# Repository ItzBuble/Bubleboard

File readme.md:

# Bubleboard

A custom full-size (104-key) mechanical keyboard with a hand-designed PCB, a rotary encoder, an e-ink display and [ZMK](https://zmk.dev) firmware. It was built as my graduation project (maturitní práce) at SPŠ a OA Uherský Brod, field Mechanik elektrotechnik, 2026.

## Features

- 104 keys in a 21 × 6 diode matrix (N-key rollover, no ghosting)
- Seeed XIAO BLE nRF52840 microcontroller soldered directly on the PCB
- Wired USB and Bluetooth Low Energy, with a LiPo battery connected through a JST connector
- Two MCP23017 I/O expanders (I²C) to drive the matrix
- Bourns PEC11L rotary encoder (15 mm) used as a media knob
- nice!view e-ink display (SPI) showing the keyboard status
- Hot-swappable Kailh Choc V1 sockets
- Custom 2-layer PCB designed in KiCad
- 3D-printed case and keycaps
- No backlight, to keep power consumption low

## Hardware

| Part | Component |
| --- | --- |
| Microcontroller | Seeed XIAO BLE nRF52840 |
| I/O expanders | 2× MCP23017 (SSOP), I²C with 10 kΩ pull-ups |
| Switch sockets | 104× Kailh Choc V1 hot-swap |
| Matrix diodes | 105× 1N4148W |
| Rotary encoder | Bourns PEC11L, push button wired into the matrix (Column 16 / Row 0) |
| Display | nice!view, connected over SPI |
| Decoupling | 2× 100 nF and 1× 10 µF |

The PCB was made by JLCPCB and assembled by hand. The schematic and PCB use the [marbastlib](https://github.com/ebastler/marbastlib) library, and the key positions come from a [Keyboard Layout Editor](http://www.keyboard-layout-editor.com) file imported into KiCad.

## Firmware

The firmware is built on ZMK (Zephyr). The matrix is defined in the keyboard's devicetree: columns 0–15 and 16–20 are spread over the two MCP23017 expanders, rows 0–5 are on the second expander, and all pins use `GPIO_ACTIVE_LOW` with pull-ups.

Encoder functions:

- Rotate right: volume up
- Rotate left: volume down
- Press: play / pause

### Building

Firmware is built with GitHub Actions using the standard ZMK user-config workflow. Push a commit (or run the workflow manually from the **Actions** tab) and download the firmware from the build artifacts.

The build uses:

- Board: `seeeduino_xiao_ble`
- Shield: `buble_board` plus `nice_view_adapter` and `nice_view`

The ZMK build needs `config/`, `boards/` and `zephyr/module.yml` to stay in the repository root.

## Case and keycaps

The case was modelled in Autodesk Fusion and 3D printed. It is printed in two halves that are glued together in the middle, with alignment holes and pegs. The PCB is mounted on six screw posts, and a separate display holder (adapted from a freely available model) slides into V-shaped tabs in the top right corner. The keycaps are also 3D printed, adapted from existing models.

## Measurements

Power consumption while connected to a PC (no backlight, no heavy load):

| Meter | V | A | W |
| --- | --- | --- | --- |
| Custom USB meter | 5.092 | 0.005 | 0.027 |
| Commercial USB meter | 5.1080 | 0.0050 | 0.0252 |

Input latency, measured with a 240 fps phone camera (1 frame ≈ 4.167 ms):

| Keyboard | Frames | Latency |
| --- | --- | --- |
| SteelSeries Apex Pro (magnetic) | 8 | 33.3 ms |
| Bubleboard | 11 | 45.8 ms |
| Razer Ornata Chroma (membrane) | 17 | 70.8 ms |
| School membrane keyboard | 19 | 79.2 ms |

## Author

Martin Janíček. Střední průmyslová škola a obchodní akademie Uherský Brod, 2026.

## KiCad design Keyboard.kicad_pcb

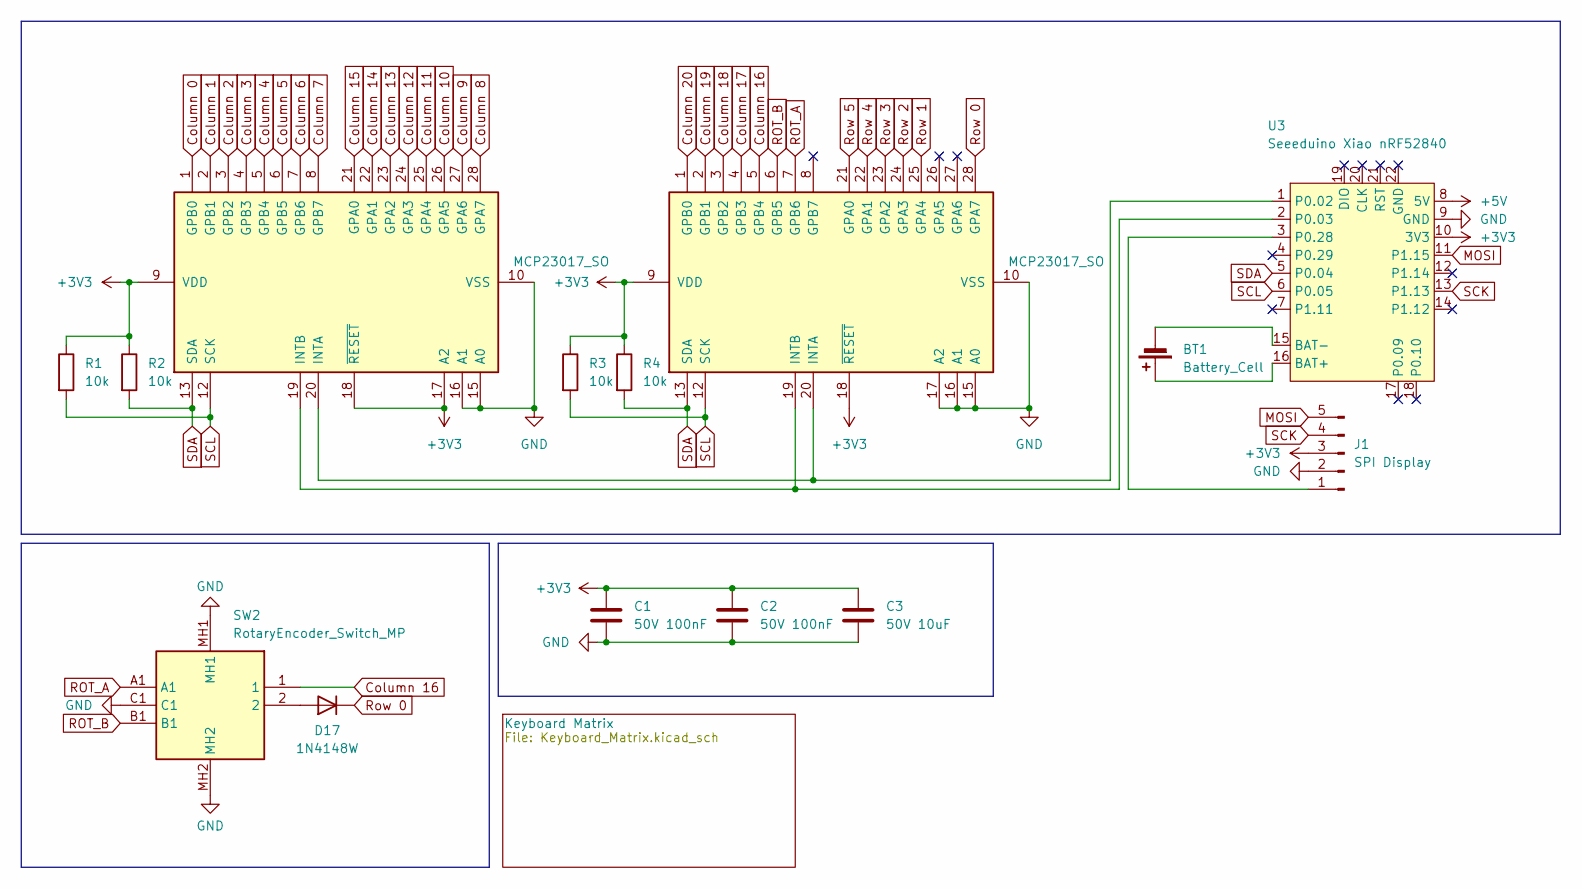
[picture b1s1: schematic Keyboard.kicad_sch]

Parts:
BT1: Battery_Cell
C1, C2: 50V 100nF; C_1206_3216Metric_Pad1.33x1.80mm_HandSolder
C3: 50V 10uF; C_1206_3216Metric_Pad1.33x1.80mm_HandSolder
D17: 1N4148W; D_SOD-123
J1: SPI Display
R1, R2, R3, R4: 10k; R_1206_3216Metric_Pad1.30x1.75mm_HandSolder
SW2: RotaryEncoder_Switch_MP; PEC11L4115FS0020; Mouser Part Number 652-PEC11L4115FS0020
U1, U2: MCP23017_SO; SOIC-28W_7.5x17.9mm_P1.27mm
U3: Seeeduino Xiao nRF52840; Xiao_nRF52840_ACH

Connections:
+3V3: C1.1, C2.1, C3.1, J1.3, R1.1, R2.1, R3.1, R4.1, U1.9 (VDD), U1.17 (A2), U1.18 (~RESET), U2.9 (VDD), U2.18 (~RESET), U3.10 (3V3)
+5V: U3.8 (5V)
Column 0: U1.1 (GPB0); also elsewhere on the board
Column 1: U1.2 (GPB1); also elsewhere on the board
Column 2: U1.3 (GPB2); also elsewhere on the board
Column 3: U1.4 (GPB3); also elsewhere on the board
Column 4: U1.5 (GPB4); also elsewhere on the board
Column 5: U1.6 (GPB5); also elsewhere on the board
Column 6: U1.7 (GPB6); also elsewhere on the board
Column 7: U1.8 (GPB7); also elsewhere on the board
Column 8: U1.28 (GPA7); also elsewhere on the board
Column 9: U1.27 (GPA6); also elsewhere on the board
Column 10: U1.26 (GPA5); also elsewhere on the board
Column 11: U1.25 (GPA4); also elsewhere on the board
Column 12: U1.24 (GPA3); also elsewhere on the board
Column 13: U1.23 (GPA2); also elsewhere on the board
Column 14: U1.22 (GPA1); also elsewhere on the board
Column 15: U1.21 (GPA0); also elsewhere on the board
Column 16: SW2.1, U2.5 (GPB4); also elsewhere on the board
Column 17: U2.4 (GPB3); also elsewhere on the board
Column 18: U2.3 (GPB2); also elsewhere on the board
Column 19: U2.2 (GPB1); also elsewhere on the board
Column 20: U2.1 (GPB0); also elsewhere on the board
GND: C1.2, C2.2, C3.2, J1.2, SW2.C1, SW2.MH1, SW2.MH2, U1.10 (VSS), U1.15 (A0), U1.16 (A1), U2.10 (VSS), U2.15 (A0), U2.16 (A1), U2.17 (A2), U3.9 (GND)
MOSI: J1.5, U3.11 (P1.15)
unnamed: D17.2 (A), SW2.2
unnamed: J1.1, U3.3 (P0.28)
unnamed: BT1.1 (+), U3.16 (BAT+)
unnamed: BT1.2 (-), U3.15 (BAT-)
ROT_A: SW2.A1, U2.7 (GPB6), U3.4 (P0.29)
ROT_B: SW2.B1, U2.6 (GPB5), U3.7 (P1.11)
Row 0: D17.1 (K), U2.28 (GPA7); also elsewhere on the board
Row 1: U2.25 (GPA4); also elsewhere on the board
Row 2: U2.24 (GPA3); also elsewhere on the board
Row 3: U2.23 (GPA2); also elsewhere on the board
Row 4: U2.22 (GPA1); also elsewhere on the board
Row 5: U2.21 (GPA0); also elsewhere on the board
SCK: J1.4, U3.13 (P1.13)
SCL: R1.2, R3.2, U1.12 (SCK), U2.12 (SCK), U3.6 (P0.05)
SDA: R2.2, R4.2, U1.13 (SDA), U2.13 (SDA), U3.5 (P0.04)

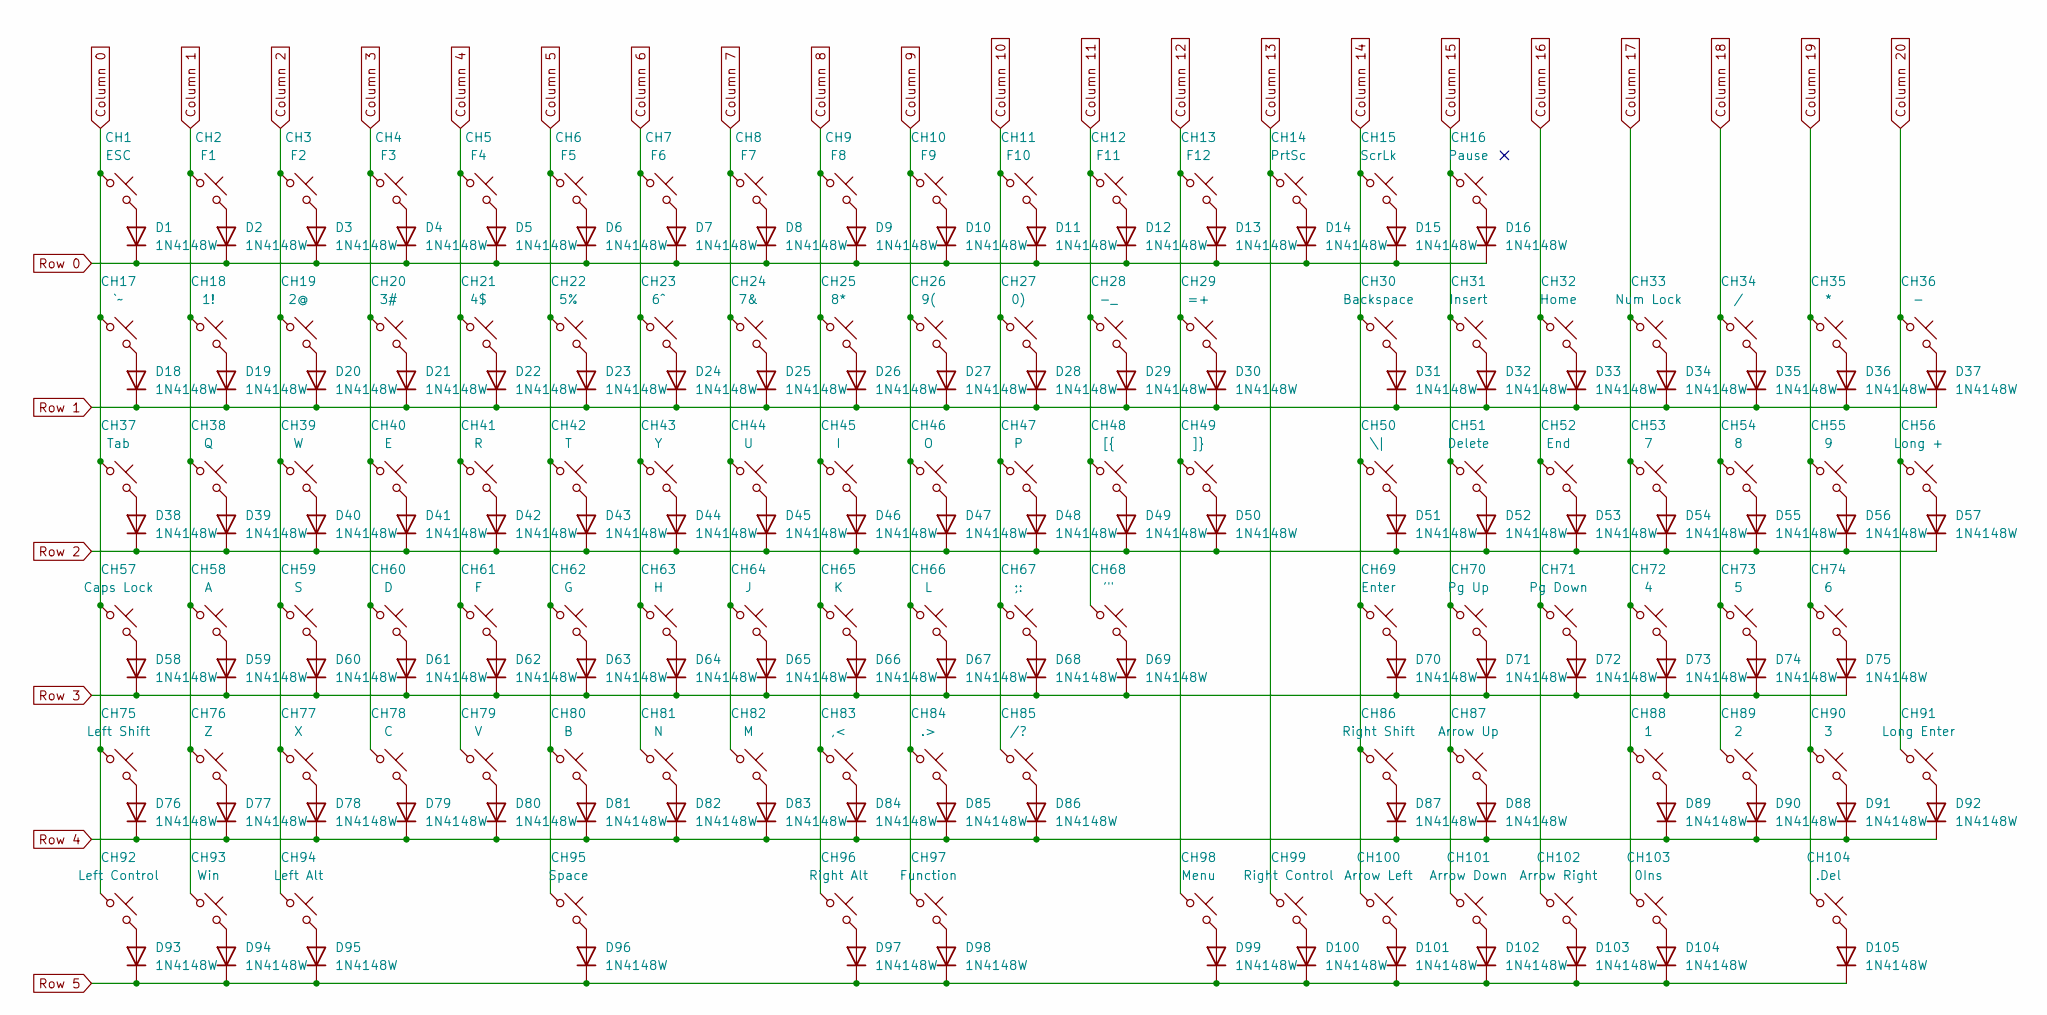
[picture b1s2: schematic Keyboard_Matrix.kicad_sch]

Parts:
CH1: ESC; SW_choc_v1_HS_CPG135001S30_1u
CH2: F1; SW_choc_v1_HS_CPG135001S30_1u
CH3: F2; SW_choc_v1_HS_CPG135001S30_1u
CH4: F3; SW_choc_v1_HS_CPG135001S30_1u
CH5: F4; SW_choc_v1_HS_CPG135001S30_1u
CH6: F5; SW_choc_v1_HS_CPG135001S30_1u
CH7: F6; SW_choc_v1_HS_CPG135001S30_1u
CH8: F7; SW_choc_v1_HS_CPG135001S30_1u
CH9: F8; SW_choc_v1_HS_CPG135001S30_1u
CH10: F9; SW_choc_v1_HS_CPG135001S30_1u
CH11: F10; SW_choc_v1_HS_CPG135001S30_1u
CH12: F11; SW_choc_v1_HS_CPG135001S30_1u
CH13: F12; SW_choc_v1_HS_CPG135001S30_1u
CH14: PrtSc; SW_choc_v1_HS_CPG135001S30_1u
CH15: ScrLk; SW_choc_v1_HS_CPG135001S30_1u
CH16: Pause; SW_choc_v1_HS_CPG135001S30_1u
CH17: `~; SW_choc_v1_HS_CPG135001S30_1u
CH18: 1!; SW_choc_v1_HS_CPG135001S30_1u
CH19: 2@; SW_choc_v1_HS_CPG135001S30_1u
CH20: 3#; SW_choc_v1_HS_CPG135001S30_1u
CH21: 4$; SW_choc_v1_HS_CPG135001S30_1u
CH22: 5%; SW_choc_v1_HS_CPG135001S30_1u
CH23: 6^; SW_choc_v1_HS_CPG135001S30_1u
CH24: 7&; SW_choc_v1_HS_CPG135001S30_1u
CH25: 8*; SW_choc_v1_HS_CPG135001S30_1u
CH26: 9(; SW_choc_v1_HS_CPG135001S30_1u
CH27: 0); SW_choc_v1_HS_CPG135001S30_1u
CH28: -_; SW_choc_v1_HS_CPG135001S30_1u
CH29: =+; SW_choc_v1_HS_CPG135001S30_1u
CH30: Backspace; SW_choc_v1_HS_CPG135001S30_1u
CH31: Insert; SW_choc_v1_HS_CPG135001S30_1u
CH32: Home; SW_choc_v1_HS_CPG135001S30_1u
CH33: Num Lock; SW_choc_v1_HS_CPG135001S30_1u
CH34: /; SW_choc_v1_HS_CPG135001S30_1u
CH35: *; SW_choc_v1_HS_CPG135001S30_1u
CH36: -; SW_choc_v1_HS_CPG135001S30_1u
CH37: Tab; SW_choc_v1_HS_CPG135001S30_1u
CH38: Q; SW_choc_v1_HS_CPG135001S30_1u
CH39: W; SW_choc_v1_HS_CPG135001S30_1u
CH40: E; SW_choc_v1_HS_CPG135001S30_1u
CH41: R; SW_choc_v1_HS_CPG135001S30_1u
CH42: T; SW_choc_v1_HS_CPG135001S30_1u
CH43: Y; SW_choc_v1_HS_CPG135001S30_1u
CH44: U; SW_choc_v1_HS_CPG135001S30_1u
CH45: I; SW_choc_v1_HS_CPG135001S30_1u
CH46: O; SW_choc_v1_HS_CPG135001S30_1u
CH47: P; SW_choc_v1_HS_CPG135001S30_1u
CH48: [{; SW_choc_v1_HS_CPG135001S30_1u
CH49: ]}; SW_choc_v1_HS_CPG135001S30_1u
CH50: \|; SW_choc_v1_HS_CPG135001S30_1u
CH51: Delete; SW_choc_v1_HS_CPG135001S30_1u
CH52: End; SW_choc_v1_HS_CPG135001S30_1u
CH53: 7; SW_choc_v1_HS_CPG135001S30_1u
CH54: 8; SW_choc_v1_HS_CPG135001S30_1u
CH55: 9; SW_choc_v1_HS_CPG135001S30_1u
CH56: Long +; SW_choc_v1_HS_CPG135001S30_1u
CH57: Caps Lock; SW_choc_v1_HS_CPG135001S30_1u
CH58: A; SW_choc_v1_HS_CPG135001S30_1u
CH59: S; SW_choc_v1_HS_CPG135001S30_1u
CH60: D; SW_choc_v1_HS_CPG135001S30_1u
CH61: F; SW_choc_v1_HS_CPG135001S30_1u
CH62: G; SW_choc_v1_HS_CPG135001S30_1u
CH63: H; SW_choc_v1_HS_CPG135001S30_1u
CH64: J; SW_choc_v1_HS_CPG135001S30_1u
CH65: K; SW_choc_v1_HS_CPG135001S30_1u
CH66: L; SW_choc_v1_HS_CPG135001S30_1u
CH67: ;:; SW_choc_v1_HS_CPG135001S30_1u
CH68: '"; SW_choc_v1_HS_CPG135001S30_1u
CH69: Enter; SW_choc_v1_HS_CPG135001S30_1u
CH70: Pg Up; SW_choc_v1_HS_CPG135001S30_1u
CH71: Pg Down; SW_choc_v1_HS_CPG135001S30_1u
CH72: 4; SW_choc_v1_HS_CPG135001S30_1u
CH73: 5; SW_choc_v1_HS_CPG135001S30_1u
CH74: 6; SW_choc_v1_HS_CPG135001S30_1u
CH75: Left Shift; SW_choc_v1_HS_CPG135001S30_1u
CH76: Z; SW_choc_v1_HS_CPG135001S30_1u
CH77: X; SW_choc_v1_HS_CPG135001S30_1u
CH78: C; SW_choc_v1_HS_CPG135001S30_1u
CH79: V; SW_choc_v1_HS_CPG135001S30_1u
CH80: B; SW_choc_v1_HS_CPG135001S30_1u
CH81: N; SW_choc_v1_HS_CPG135001S30_1u
CH82: M; SW_choc_v1_HS_CPG135001S30_1u
CH83: ,<; SW_choc_v1_HS_CPG135001S30_1u
CH84: .>; SW_choc_v1_HS_CPG135001S30_1u
CH85: /?; SW_choc_v1_HS_CPG135001S30_1u
CH86: Right Shift; SW_choc_v1_HS_CPG135001S30_1u
CH87: Arrow Up; SW_choc_v1_HS_CPG135001S30_1u
CH88: 1; SW_choc_v1_HS_CPG135001S30_1u
CH89: 2; SW_choc_v1_HS_CPG135001S30_1u
CH90: 3; SW_choc_v1_HS_CPG135001S30_1u
CH91: Long Enter; SW_choc_v1_HS_CPG135001S30_1u
CH92: Left Control; SW_choc_v1_HS_CPG135001S30_1u
CH93: Win; SW_choc_v1_HS_CPG135001S30_1u
CH94: Left Alt; SW_choc_v1_HS_CPG135001S30_1u
CH95: Space; SW_choc_v1_HS_CPG135001S30_1u
CH96: Right Alt; SW_choc_v1_HS_CPG135001S30_1u
CH97: Function; SW_choc_v1_HS_CPG135001S30_1u
CH98: Menu; SW_choc_v1_HS_CPG135001S30_1u
CH99: Right Control; SW_choc_v1_HS_CPG135001S30_1u
CH100: Arrow Left; SW_choc_v1_HS_CPG135001S30_1u
CH101: Arrow Down; SW_choc_v1_HS_CPG135001S30_1u
CH102: Arrow Right; SW_choc_v1_HS_CPG135001S30_1u
CH103: 0Ins; SW_choc_v1_HS_CPG135001S30_1u
CH104: .Del; SW_choc_v1_HS_CPG135001S30_1u
D1, D2, D3, D4, D5, D6, D7, D8, D9, D10, D11, D12, D13, D14, D15, D16, D18, D19, D20, D21, D22, D23, D24, D25, D26, D27, D28, D29, D30, D31, D32, D33, D34, D35, D36, D37, D38, D39, D40, D41, D42, D43, D44, D45, D46, D47, D48, D49, D50, D51, D52, D53, D54, D55, D56, D57, D58, D59, D60, D61, D62, D63, D64, D65, D66, D67, D68, D69, D70, D71, D72, D73, D74, D75, D76, D77, D78, D79, D80, D81, D82, D83, D84, D85, D86, D87, D88, D89, D90, D91, D92, D93, D94, D95, D96, D97, D98, D99, D100, D101, D102, D103, D104, D105: 1N4148W; D_SOD-123

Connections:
Column 0: CH1.1, CH17.1, CH37.1, CH57.1, CH75.1, CH92.1; also elsewhere on the board
Column 1: CH2.1, CH18.1, CH38.1, CH58.1, CH76.1, CH93.1; also elsewhere on the board
Column 2: CH3.1, CH19.1, CH39.1, CH59.1, CH77.1, CH94.1; also elsewhere on the board
Column 3: CH4.1, CH20.1, CH40.1, CH60.1, CH78.1; also elsewhere on the board
Column 4: CH5.1, CH21.1, CH41.1, CH61.1, CH79.1; also elsewhere on the board
Column 5: CH6.1, CH22.1, CH42.1, CH62.1, CH80.1, CH95.1; also elsewhere on the board
Column 6: CH7.1, CH23.1, CH43.1, CH63.1, CH81.1; also elsewhere on the board
Column 7: CH8.1, CH24.1, CH44.1, CH64.1, CH82.1; also elsewhere on the board
Column 8: CH9.1, CH25.1, CH45.1, CH65.1, CH83.1, CH96.1; also elsewhere on the board
Column 9: CH10.1, CH26.1, CH46.1, CH66.1, CH84.1, CH97.1; also elsewhere on the board
Column 10: CH11.1, CH27.1, CH47.1, CH67.1, CH85.1; also elsewhere on the board
Column 11: CH12.1, CH28.1, CH48.1, CH68.1; also elsewhere on the board
Column 12: CH13.1, CH29.1, CH49.1, CH98.1; also elsewhere on the board
Column 13: CH14.1, CH99.1; also elsewhere on the board
Column 14: CH15.1, CH30.1, CH50.1, CH69.1, CH86.1, CH100.1; also elsewhere on the board
Column 15: CH16.1, CH31.1, CH51.1, CH70.1, CH87.1, CH101.1; also elsewhere on the board
Column 16: CH32.1, CH52.1, CH71.1, CH102.1; also elsewhere on the board
Column 17: CH33.1, CH53.1, CH72.1, CH88.1, CH103.1; also elsewhere on the board
Column 18: CH34.1, CH54.1, CH73.1, CH89.1; also elsewhere on the board
Column 19: CH35.1, CH55.1, CH74.1, CH90.1, CH104.1; also elsewhere on the board
Column 20: CH36.1, CH56.1, CH91.1; also elsewhere on the board
unnamed: CH1.2, D1.2 (A)
unnamed: CH2.2, D2.2 (A)
unnamed: CH3.2, D3.2 (A)
unnamed: CH4.2, D4.2 (A)
unnamed: CH5.2, D5.2 (A)
unnamed: CH6.2, D6.2 (A)
unnamed: CH7.2, D7.2 (A)
unnamed: CH8.2, D8.2 (A)
unnamed: CH9.2, D9.2 (A)
unnamed: CH10.2, D10.2 (A)
unnamed: CH11.2, D11.2 (A)
unnamed: CH12.2, D12.2 (A)
unnamed: CH13.2, D13.2 (A)
unnamed: CH14.2, D14.2 (A)
unnamed: CH15.2, D15.2 (A)
unnamed: CH16.2, D16.2 (A)
unnamed: CH17.2, D18.2 (A)
unnamed: CH18.2, D19.2 (A)
unnamed: CH19.2, D20.2 (A)
unnamed: CH20.2, D21.2 (A)
unnamed: CH21.2, D22.2 (A)
unnamed: CH22.2, D23.2 (A)
unnamed: CH23.2, D24.2 (A)
unnamed: CH24.2, D25.2 (A)
unnamed: CH25.2, D26.2 (A)
unnamed: CH26.2, D27.2 (A)
unnamed: CH27.2, D28.2 (A)
unnamed: CH28.2, D29.2 (A)
unnamed: CH29.2, D30.2 (A)
unnamed: CH30.2, D31.2 (A)
unnamed: CH31.2, D32.2 (A)
unnamed: CH32.2, D33.2 (A)
unnamed: CH33.2, D34.2 (A)
unnamed: CH34.2, D35.2 (A)
unnamed: CH35.2, D36.2 (A)
unnamed: CH36.2, D37.2 (A)
unnamed: CH37.2, D38.2 (A)
unnamed: CH38.2, D39.2 (A)
unnamed: CH39.2, D40.2 (A)
unnamed: CH40.2, D41.2 (A)
unnamed: CH41.2, D42.2 (A)
unnamed: CH42.2, D43.2 (A)
unnamed: CH43.2, D44.2 (A)
unnamed: CH44.2, D45.2 (A)
unnamed: CH45.2, D46.2 (A)
unnamed: CH46.2, D47.2 (A)
unnamed: CH47.2, D48.2 (A)
unnamed: CH48.2, D49.2 (A)
unnamed: CH49.2, D50.2 (A)
unnamed: CH50.2, D51.2 (A)
unnamed: CH51.2, D52.2 (A)
unnamed: CH52.2, D53.2 (A)
unnamed: CH53.2, D54.2 (A)
unnamed: CH54.2, D55.2 (A)
unnamed: CH55.2, D56.2 (A)
unnamed: CH56.2, D57.2 (A)
unnamed: CH57.2, D58.2 (A)
unnamed: CH58.2, D59.2 (A)
unnamed: CH59.2, D60.2 (A)
unnamed: CH60.2, D61.2 (A)
unnamed: CH61.2, D62.2 (A)
unnamed: CH62.2, D63.2 (A)
unnamed: CH63.2, D64.2 (A)
unnamed: CH64.2, D65.2 (A)
unnamed: CH65.2, D66.2 (A)
unnamed: CH66.2, D67.2 (A)
unnamed: CH67.2, D68.2 (A)
unnamed: CH68.2, D69.2 (A)
unnamed: CH69.2, D70.2 (A)
unnamed: CH70.2, D71.2 (A)
unnamed: CH71.2, D72.2 (A)
unnamed: CH72.2, D73.2 (A)
unnamed: CH73.2, D74.2 (A)
unnamed: CH74.2, D75.2 (A)
unnamed: CH75.2, D76.2 (A)
unnamed: CH76.2, D77.2 (A)
unnamed: CH77.2, D78.2 (A)
unnamed: CH78.2, D79.2 (A)
unnamed: CH79.2, D80.2 (A)
unnamed: CH80.2, D81.2 (A)
unnamed: CH81.2, D82.2 (A)
unnamed: CH82.2, D83.2 (A)
unnamed: CH83.2, D84.2 (A)
unnamed: CH84.2, D85.2 (A)
unnamed: CH85.2, D86.2 (A)
unnamed: CH86.2, D87.2 (A)
unnamed: CH87.2, D88.2 (A)
unnamed: CH88.2, D89.2 (A)
unnamed: CH89.2, D90.2 (A)
unnamed: CH90.2, D91.2 (A)
unnamed: CH91.2, D92.2 (A)
unnamed: CH92.2, D93.2 (A)
unnamed: CH93.2, D94.2 (A)
unnamed: CH94.2, D95.2 (A)
unnamed: CH95.2, D96.2 (A)
unnamed: CH96.2, D97.2 (A)
unnamed: CH97.2, D98.2 (A)
unnamed: CH98.2, D99.2 (A)
unnamed: CH99.2, D100.2 (A)
unnamed: CH100.2, D101.2 (A)
unnamed: CH101.2, D102.2 (A)
unnamed: CH102.2, D103.2 (A)
unnamed: CH103.2, D104.2 (A)
unnamed: CH104.2, D105.2 (A)
Row 0: D1.1 (K), D2.1 (K), D3.1 (K), D4.1 (K), D5.1 (K), D6.1 (K), D7.1 (K), D8.1 (K), D9.1 (K), D10.1 (K), D11.1 (K), D12.1 (K), D13.1 (K), D14.1 (K), D15.1 (K), D16.1 (K); also elsewhere on the board
Row 1: D18.1 (K), D19.1 (K), D20.1 (K), D21.1 (K), D22.1 (K), D23.1 (K), D24.1 (K), D25.1 (K), D26.1 (K), D27.1 (K), D28.1 (K), D29.1 (K), D30.1 (K), D31.1 (K), D32.1 (K), D33.1 (K), D34.1 (K), D35.1 (K), D36.1 (K), D37.1 (K); also elsewhere on the board
Row 2: D38.1 (K), D39.1 (K), D40.1 (K), D41.1 (K), D42.1 (K), D43.1 (K), D44.1 (K), D45.1 (K), D46.1 (K), D47.1 (K), D48.1 (K), D49.1 (K), D50.1 (K), D51.1 (K), D52.1 (K), D53.1 (K), D54.1 (K), D55.1 (K), D56.1 (K), D57.1 (K); also elsewhere on the board
Row 3: D58.1 (K), D59.1 (K), D60.1 (K), D61.1 (K), D62.1 (K), D63.1 (K), D64.1 (K), D65.1 (K), D66.1 (K), D67.1 (K), D68.1 (K), D69.1 (K), D70.1 (K), D71.1 (K), D72.1 (K), D73.1 (K), D74.1 (K), D75.1 (K); also elsewhere on the board
Row 4: D76.1 (K), D77.1 (K), D78.1 (K), D79.1 (K), D80.1 (K), D81.1 (K), D82.1 (K), D83.1 (K), D84.1 (K), D85.1 (K), D86.1 (K), D87.1 (K), D88.1 (K), D89.1 (K), D90.1 (K), D91.1 (K), D92.1 (K); also elsewhere on the board
Row 5: D93.1 (K), D94.1 (K), D95.1 (K), D96.1 (K), D97.1 (K), D98.1 (K), D99.1 (K), D100.1 (K), D101.1 (K), D102.1 (K), D103.1 (K), D104.1 (K), D105.1 (K); also elsewhere on the board

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
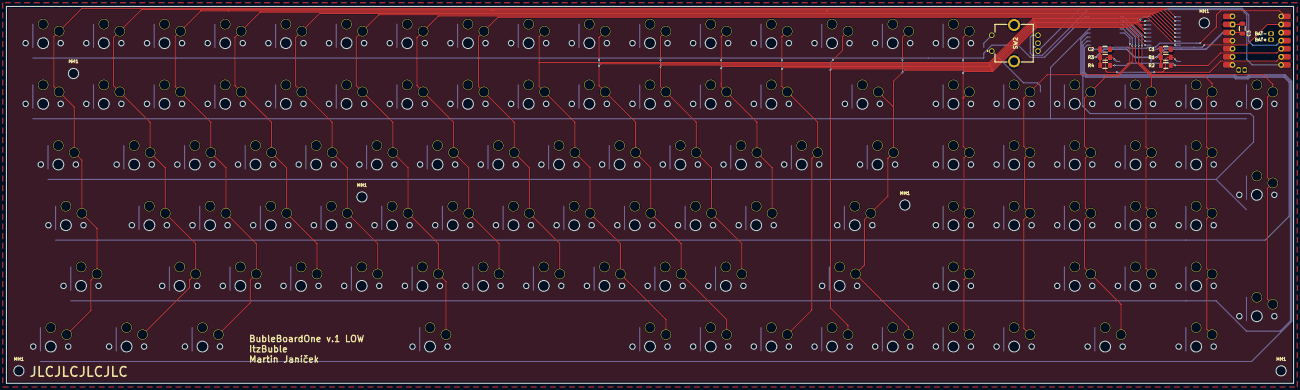
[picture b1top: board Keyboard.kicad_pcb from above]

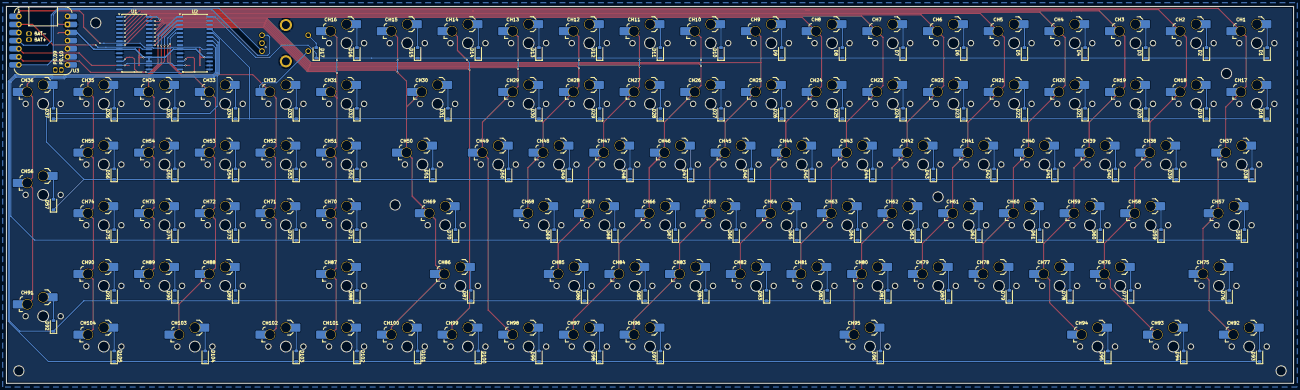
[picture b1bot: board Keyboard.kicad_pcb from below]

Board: 2 copper layers, 404.0 x 118.3 mm, 226 parts (212 on the bottom side), 140 nets.

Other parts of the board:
MH1, MH1#2, MH1#3, MH1#4, MH1#5, MH1#6: MountingHole_3.2mm_M3_ISO14580

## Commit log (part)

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2025-09-09 Added .gitignore file
2025-09-09 Removed useless files from the repo
2025-09-09 Added the OLED SPI Display and remade the entire PCB
2025-09-09 Fixed warnings about silkscreen clipping with the solder mask
2025-09-09 Added PDF exports of the schematic and the PCB to allow easy viewing without using kicad
2025-09-10 Added Mounting Holes to the PCB
2025-09-10 Flipped the Seeed Xiao
2025-09-18 Added the Display holder 3D model for the case.
2025-09-18 Minor update.
2025-09-18 Fixed battery symbol errors.
2025-09-18 Made little design changes to the schematic.
2025-09-18 Added text to the pcb.
2025-09-18 Updated footprints.
2025-09-18 Replaced Rotary Encoder.
2025-10-02 Changed routing.
2025-10-13 Fixed issues with JLCDFM.
2025-10-13 Added .lck files to .gitignore.
